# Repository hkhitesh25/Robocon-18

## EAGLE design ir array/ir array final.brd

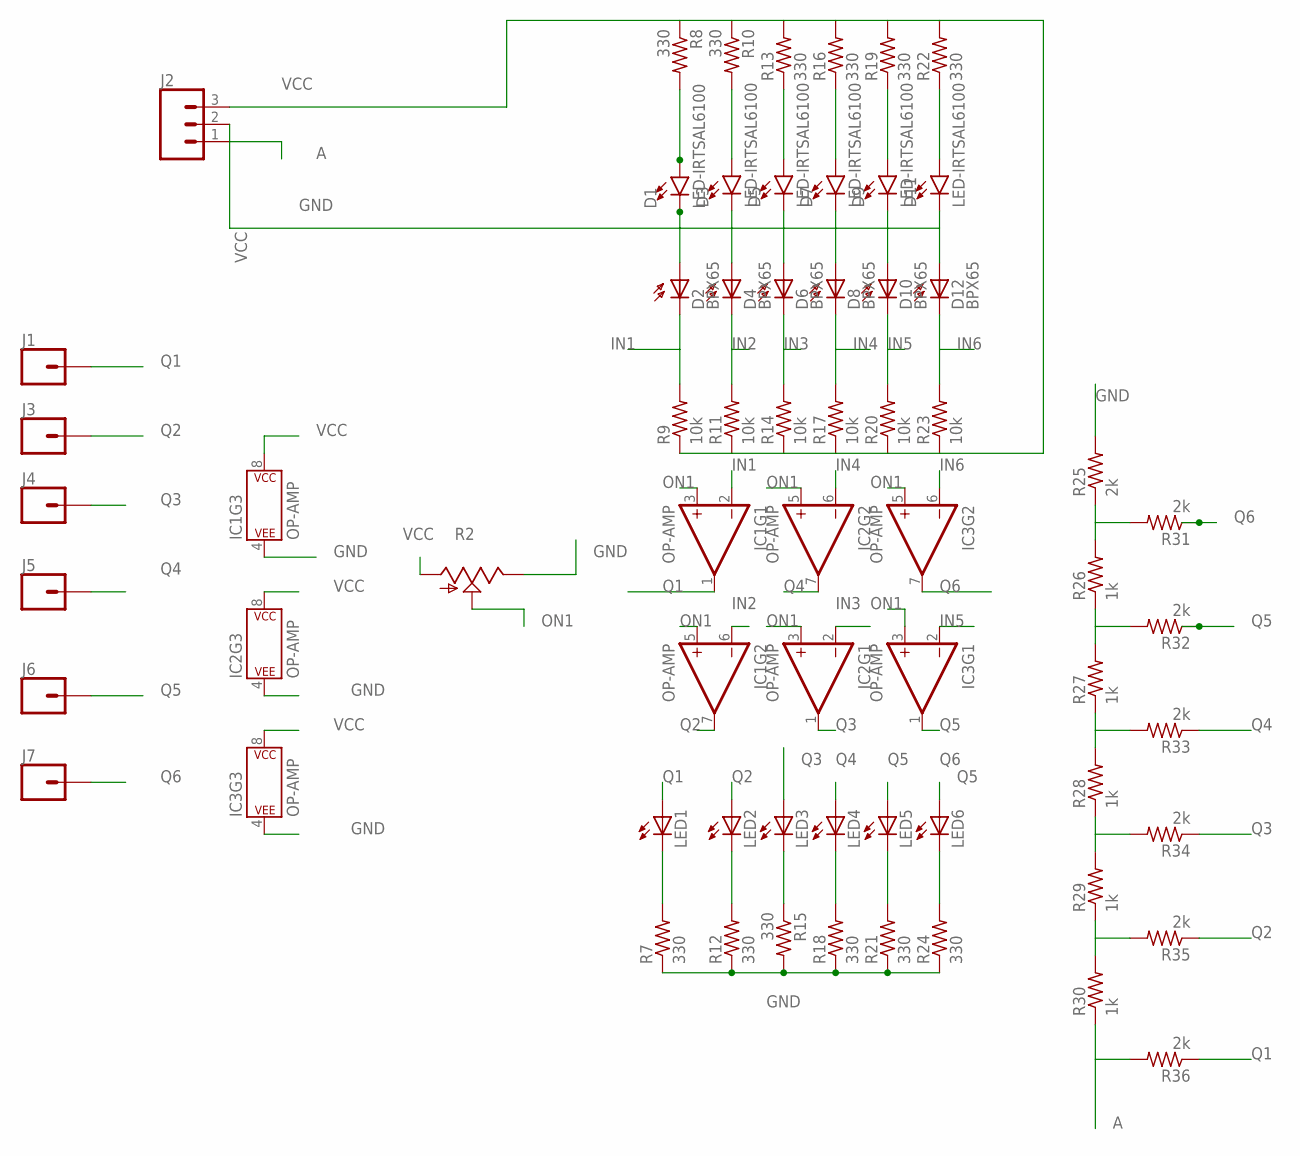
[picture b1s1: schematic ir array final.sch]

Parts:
D1, D3, D5, D7, D9, D11: LED-IRTSAL6100; LED_5MM
D2, D4, D6, D8, D10, D12: BPX65
IC1, IC2, IC3: OP-AMP; DIP08
J1, J3, J4, J5, J6, J7: CONN_01; 1X01
J2: CONN_03; 1X03
LED1, LED2, LED3, LED4, LED5, LED6: LED3MM
R2: TRIM_US-CA6V; CA6V
R7, R8, R10, R12, R13, R15, R16, R18, R19, R21, R22, R24: 330; 0207/9
R9, R11, R14, R17, R20, R23: 10k; 0207/9
R25, R31, R32, R33, R34, R35, R36: 2k; 0207/9
R26, R27, R28, R29, R30: 1k; 0207/9

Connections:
A: J2.1, R30.1, R36.2
GND: D1.K (C), D2.A, D3.K (C), D4.A, D5.K (C), D6.A, D7.K (C), D8.A, D9.K (C), D10.A, D11.K (C), D12.A, IC1.4 (P$V-), IC2.4 (P$V-), IC3.4 (P$V-), J2.2, R2.E, R7.1, R12.1, R15.2, R18.1, R21.1, R24.1, R25.2
IN1: D2.K (C), IC1.2 (-IN), R9.2
IN2: D4.K (C), IC1.6 (-IN), R11.2
IN3: D6.K (C), IC2.2 (-IN), R14.2
IN4: D8.K (C), IC2.6 (-IN), R17.2
IN5: D10.K (C), IC3.2 (-IN), R20.2
IN6: D12.K (C), IC3.6 (-IN), R23.2
unnamed: D1.A, R8.2
unnamed: D3.A, R10.2
unnamed: D5.A, R13.1
unnamed: D7.A, R16.1
unnamed: D9.A, R19.1
unnamed: D11.A, R22.1
unnamed: LED1.K (C), R7.2
unnamed: LED2.K (C), R12.2
unnamed: LED3.K (C), R15.1
unnamed: LED4.K (C), R18.2
unnamed: LED5.K (C), R21.2
unnamed: LED6.K (C), R24.2
unnamed: R25.1, R26.2, R31.2
unnamed: R26.1, R27.2, R32.2
unnamed: R27.1, R28.2, R33.2
unnamed: R28.1, R29.2, R34.2
unnamed: R29.1, R30.2, R35.2
ON1: IC1.3 (+IN), IC1.5 (+IN), IC2.3 (+IN), IC2.5 (+IN), IC3.3 (+IN), IC3.5 (+IN), R2.S
Q1: IC1.1 (OUT), J1.1, LED1.A, R36.1
Q2: IC1.7 (OUT), J3.1, LED2.A, R35.1
Q3: IC2.1 (OUT), J4.1, LED3.A, R34.1
Q4: IC2.7 (OUT), J5.1, LED4.A, R33.1
Q5: IC3.1 (OUT), J6.1, LED5.A, R32.1
Q6: IC3.7 (OUT), J7.1, LED6.A, R31.1
VCC: IC1.8 (P$V+), IC2.8 (P$V+), IC3.8 (P$V+), J2.3, R2.A, R8.1, R9.1, R10.1, R11.1, R13.2, R14.1, R16.2, R17.1, R19.2, R20.1, R22.2, R23.1

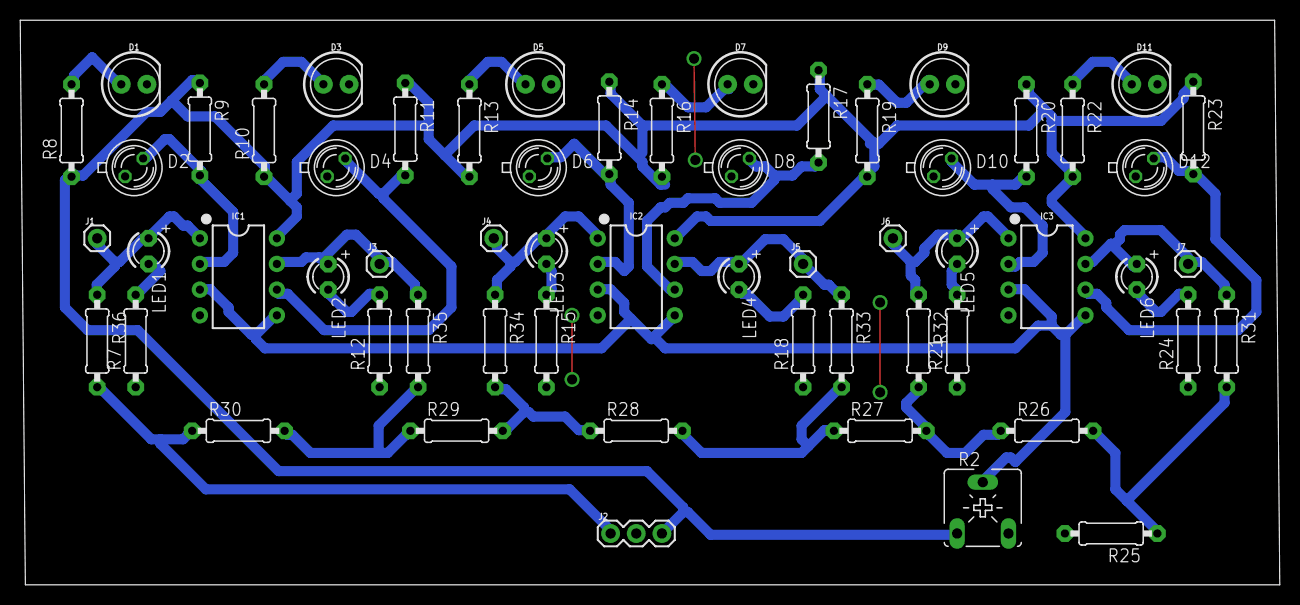
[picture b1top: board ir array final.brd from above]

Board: 2 copper layers, 124.6 x 55.9 mm, 59 parts (0 on the bottom side), 33 nets.

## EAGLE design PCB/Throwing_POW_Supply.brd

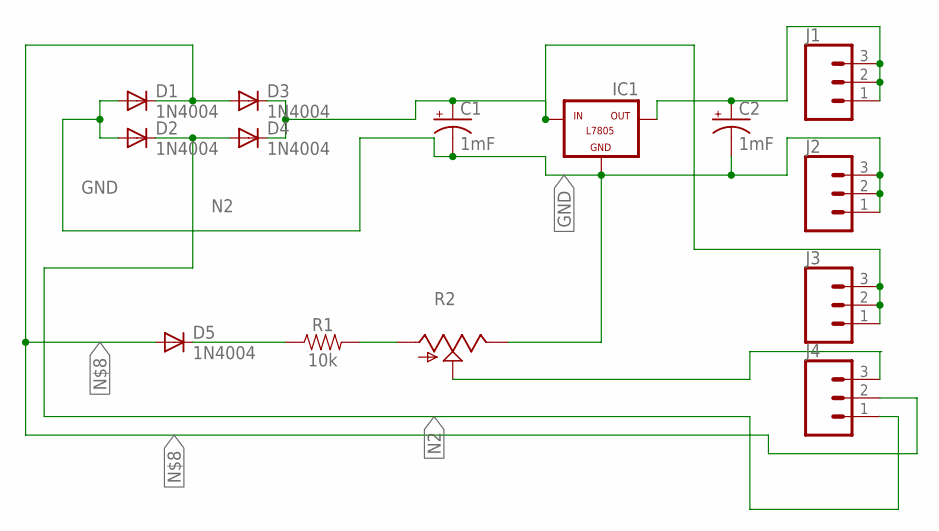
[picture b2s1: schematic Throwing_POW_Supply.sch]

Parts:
C1, C2: 1mF; CPOL-RADIAL-5MM-10MM
D1, D2, D3, D4, D5: 1N4004; DO41-10
IC1: L7805; 78XXL
J1, J2, J3, J4: CONN_03; 1X03
R1: 10k; AXIAL-0.3
R2: TRIM_US-B25P; B25P

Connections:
GND: C1.-, C2.-, D1.A, D2.A, IC1.GND, J2.1, J2.2, J2.3, R2.E
N2: D2.C, D4.A, J4.1
unnamed: C2.+, IC1.OUT, J1.1, J1.2, J1.3
unnamed: D5.C, R1.P$1 (1)
unnamed: R1.P$2 (2), R2.A
unnamed: C1.+, D3.C, D4.C, IC1.IN, J3.1, J3.2, J3.3
unnamed: J4.3, R2.S
unnamed: D1.C, D3.A, D5.A, J4.2

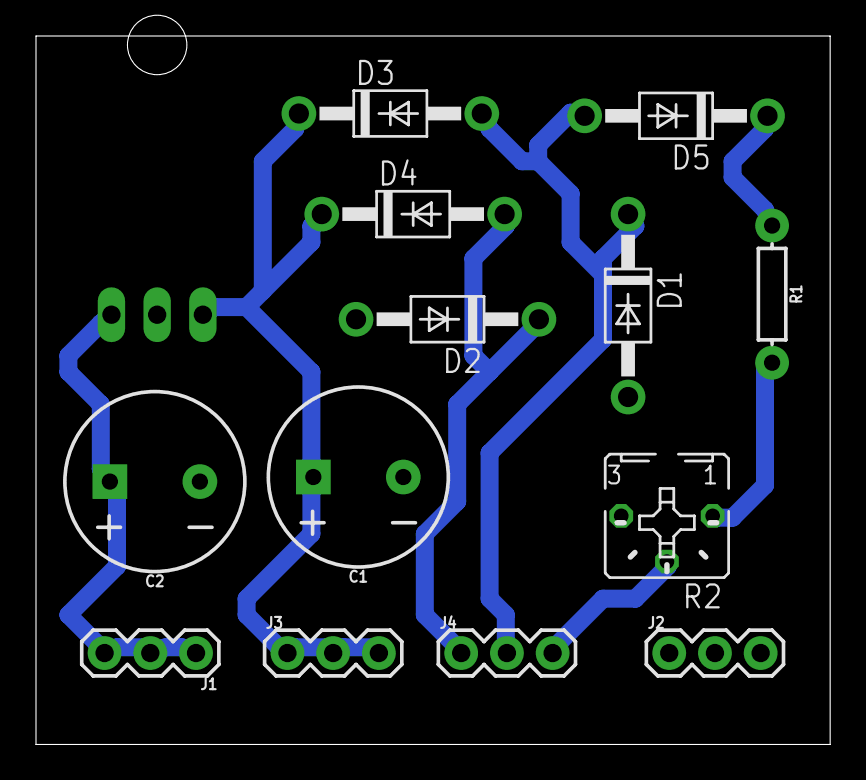
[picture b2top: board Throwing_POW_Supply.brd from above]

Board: 2 copper layers, 44.1 x 39.4 mm, 14 parts (1 on the bottom side), 8 nets.

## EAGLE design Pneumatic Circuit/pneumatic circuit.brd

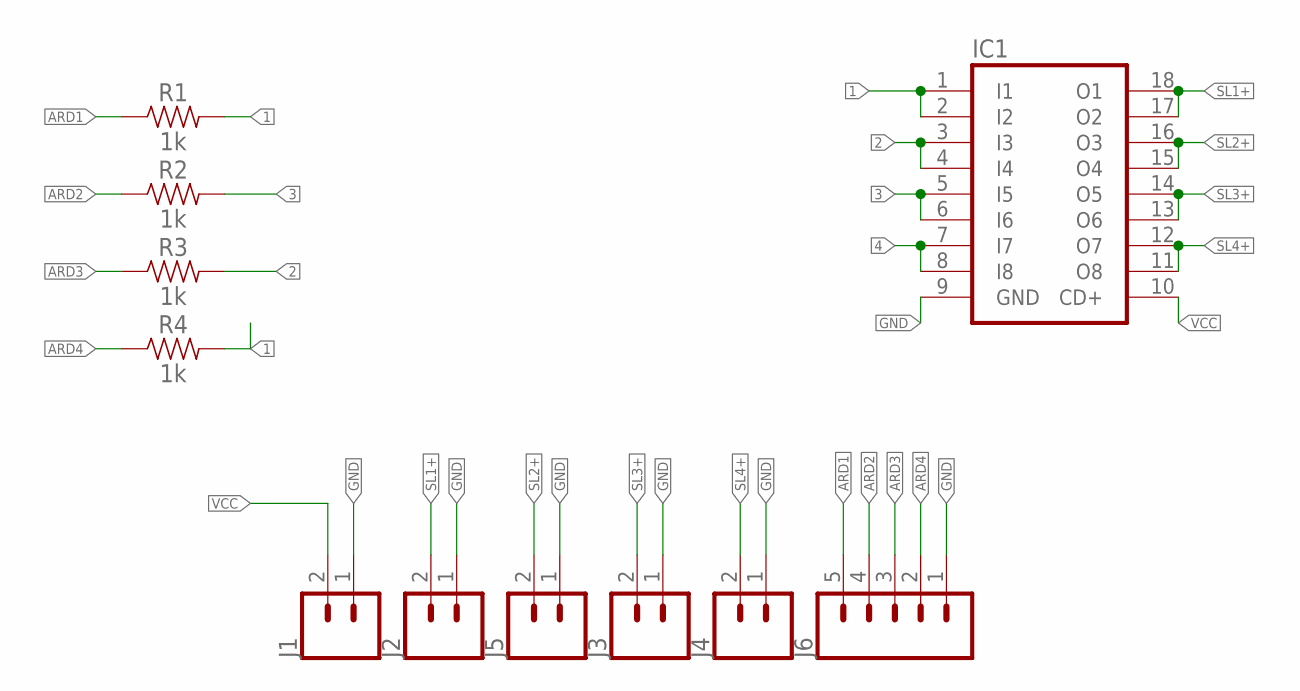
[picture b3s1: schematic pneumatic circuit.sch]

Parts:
IC1: ULN2803A; DIL18
J1, J2, J3, J4, J5: CONN_023.5MM; SCREWTERMINAL-3.5MM-2
J6: CONN_05; 1X05
R1, R2, R3, R4: 1k; AXIAL-0.3

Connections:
1: IC1.1 (I1), IC1.2 (I2), R4.P$2 (2)
2: IC1.3 (I3), IC1.4 (I4), R3.P$2 (2)
3: IC1.5 (I5), IC1.6 (I6), R2.P$2 (2)
4: IC1.7 (I7), IC1.8 (I8), R1.P$2 (2)
ARD1: J6.5, R1.P$1 (1)
ARD2: J6.4, R2.P$1 (1)
ARD3: J6.3, R3.P$1 (1)
ARD4: J6.2, R4.P$1 (1)
GND: IC1.9 (GND), J1.1, J2.1, J3.1, J4.1, J5.1, J6.1
SL1+: IC1.17 (O2), IC1.18 (O1), J2.2
SL2+: IC1.15 (O4), IC1.16 (O3), J5.2
SL3+: IC1.13 (O6), IC1.14 (O5), J3.2
SL4+: IC1.11 (O8), IC1.12 (O7), J4.2
VCC: IC1.10 (CD+), J1.2

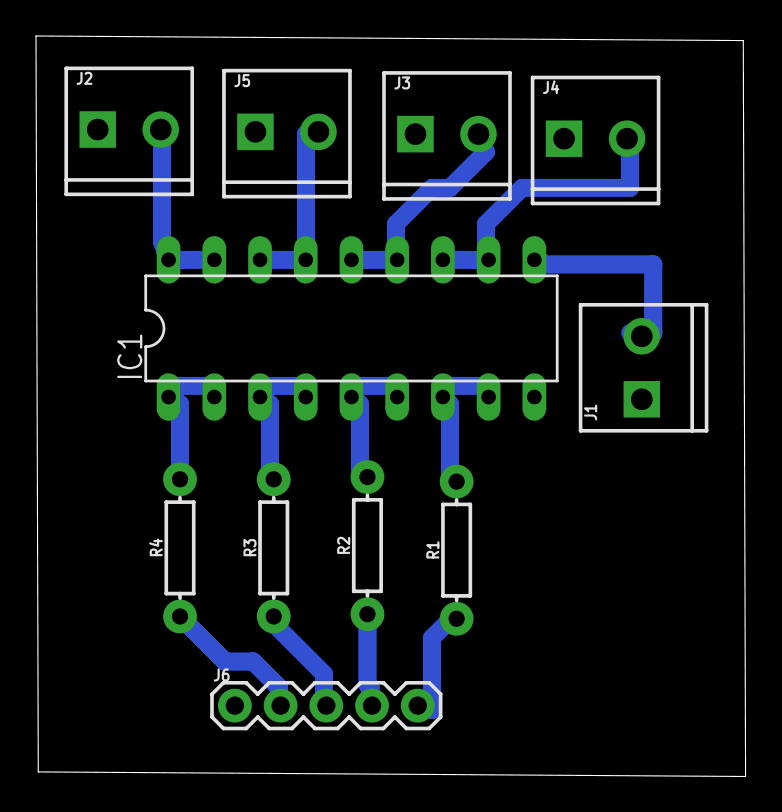
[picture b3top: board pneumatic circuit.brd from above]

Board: 2 copper layers, 39.4 x 41.1 mm, 11 parts (0 on the bottom side), 14 nets.

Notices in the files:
parts and their libraries:
SparkFun-Capacitors: Licensing: Creative Commons ShareAlike 4.0 International - https://creativecommons.org/licenses/by-sa/4.0
